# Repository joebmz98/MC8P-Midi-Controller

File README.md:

# MC8P Standalone MIDI Controller

---

# **8-Pot Standalone MIDI Controller (Teensy 4.0)**

A customizable, open-source MIDI controller with **8 potentiometers**, each supporting **Up to 10 assignable MIDI CCs per Potentiometer**, built around the **Teensy 4.0** for high-performance MIDI control.

---
## Introducing the MC8P Video

---

## **Features**
- **8x B100K Pots** with smooth analog control
- **Teensy 4.0** for fast, reliable MIDI
- **SSD1306 I2C OLED (128x64)** for the UI
- **Per-Pot CC Assignment** – Each pot can send **10 different MIDI CCs**
- **3.5mm MIDI TRS Out** (PJ307 socket for Type A MIDI)
- **4x Kailh Switches** for UI navigation/configuration
- **Standalone Operation** – No computer needed after setup
- **Open-Source Firmware** (Arduino IDE-compatible)

---

## **Bill of Materials (BOM)**

| Component                  | Qty | Notes                          | Links |
|----------------------------|-----|--------------------------------|-------|
| Teensy 4.0                 | 1   | Main microcontroller           | [The Pi Hut (UK)](https://thepihut.com/products/pjrc-teensy-4-0-usb-development-board) |
| SSD1306 OLED (128×64)      | 1   | I²C interface                  | [AliExpress](https://www.aliexpress.com/item/1005006997755041.html) |
| B100K Vertical Potentiometer | 8  | Linear taper                   | [Example](https://shorturl.at/ZGaz2) |
| 3.5mm Stereo Socket (PJ307) | 1  | MIDI TRS Type A                | [Example](https://shorturl.at/lp2T3) |
| Kailh Switches             | 4   | For menu navigation            | —     |
| Kailh Switch Caps          | 4   | For Kailh switches             | [AliExpress](https://www.aliexpress.com/item/1005006477890497.html) |
| Potentiometer Knobs        | 8   | For B100K potentiometers       | [AliExpress](https://www.aliexpress.com/item/1005006064249289.html) |
| DC-005 Barrel Jack Socket  | 1   | 5V DC power input              | [AliExpress](https://www.aliexpress.com/item/32839712664.html) |
| 10nF Ceramic Capacitors    | 8   | Potentiometer filtering        | —     |
| 10k Resistors              | 4   | Pull-down for buttons          | —     |
| 220Ω Resistors             | 2   | For MIDI Circuitry             | —     |
| 100nF Ceramic Capacitor    | 1   | Power rail stabilisation       | —     |
| 10uF Ceramic Capacitor     | 1   | Power rail stabilisation       | —     |
| 10uF Electrolytic Capacitor| 1   | 5V input stability             | —     |
| 100uF Electrolytic Capacitor | 1 | Power rail stabilisation       | —     |

---

## **Available Purchase Options**
**PCB Only** – For custom builds → [**Purchase from my Tindie store**](https://www.tindie.com/products/axsinstruments/diy-mc8p-standalone-midi-controller-pcbs-only/)

---

## **Installation & Setup**
### **1. Flashing the Firmware**
- Install **Arduino IDE + Teensyduino** and other dependencies referenced in the Building from Source section
- Clone this repo and open the `.ino` file in the Arduino IDE
- Select **Teensy 4.0** in Arduino IDE
- Upload the firmware

### **2. Hardware Assembly**
- Refer to the *Build Guide*

### **3. First Boot**
- Power via **USB** on the Teensy or via DC-005 input jack 
- Use the **OLED menu** to assign CCs

---

## **Configuration**

### Button Functions

| Button | Primary Function |
|--------|-----------------|
| ASSIGN | Navigate backward, cancel actions, return to previous screens |
| ENTER | Confirm selections, activate temporary override mode |
| PREV | Move up or decrease values |
| NEXT | Move down or increase values |

### Screen Hierarchy

The interface is organized into several screens accessible from the main display:

**MAIN SCREEN** → **MENU** → **SETTINGS** → various configuration screens

### Main Screen

This is your default operating view. The screen displays eight circular indicators, one for each potentiometer, showing current MIDI values (0-127). Each circle fills proportionally to the value being sent.

From the main screen:
- Press **ASSIGN** to open the menu
- Press and hold **ENTER** to activate temporary override mode (the display inverts as visual feedback)

### Temporary Override Mode

When you press and hold ENTER on the main screen, the controller enters temporary override mode. In this mode, all potentiometer adjustments are temporary. When you release ENTER, the controller returns to the stored values and activates catch up mode, where potentiometers must pass through their stored positions before taking control again.

### Menu Screen

Press ASSIGN from the main screen to reach the menu. Use PREV and NEXT to scroll through options:

- **CC assign** – Configure MIDI messages for each potentiometer
- **Settings** – Access device configuration

Press ENTER to select an option, or press ASSIGN to return to the main screen.

### Assign Screen (CC Assign)

This screen lets you configure up to 10 MIDI messages per potentiometer.

**Navigation flow:**
1. Select which potentiometer to edit (flashing number)
2. Select which message slot to edit, or choose Add/Remove
3. Edit individual parameters

**Parameters you can edit for each message:**
- **Channel** – MIDI channel (1-16) or OMNI
- **CC** – Control Change number (0-127)
- **Min Value** – Minimum output value (0-127)
- **Max Value** – Maximum output value (0-127)
- **Direction** – Normal (0-127) or Inverted (127-0)

**Editing values:** When editing a parameter, use potentiometer 8 to smoothly adjust the value across its full range. The selected parameter flashes to indicate edit mode.

**Navigation within Assign Screen:**
- **PREV/NEXT** – Navigate between pots, messages, or Add/Remove buttons
- **ENTER** – Enter edit mode for a parameter, or cycle to the next parameter
- **ASSIGN** – Return to pot selection, or save and exit (confirmation popup appears)

**Add/Remove messages:**
- Navigate to "+ Add" to create a new message (up to 10 per pot)
- Navigate to "- Remove" to delete the selected message (minimum 1 message per pot)

### Settings Screen

From the menu, select Settings to access:

**Assign Settings** – Choose which potentiometer (1-8) to use for editing values in the Assign screen. Use PREV/NEXT to change the selection.

**Display Settings** – Toggle the display inversion between normal and inverted. Press ENTER to enter edit mode, then use PREV or NEXT to toggle between Yes and No. Press ENTER again to save, or ASSIGN to cancel.

**About** – View firmware version and device information.

**Factory Reset** – Restore all settings to default values. A confirmation screen prevents accidental resets.

### Confirmation Popups

When saving changes or performing a factory reset, a popup screen appears asking for confirmation. Use PREV/NEXT to toggle between Y (Yes) and N (No), then press ENTER to confirm or ASSIGN to cancel.

---

## **MIDI Implementation**
- USB MIDI **OR** TRS MIDI Out (3.5mm Type A)
- Up to **10 CC Messages** per potentiometer - further expansion maybe soon!

---

## **Building from Source**
- Requires **Arduino IDE + Teensyduino**
- Libraries:
  - `Adafruit_SSD1306` (OLED)
  - `Adafruit_GFX` (Adafruit UI Design)
  - `MIDI` (MIDI)
  - `ResponsiveAnalogRead` (Potentiometer Smoothing)
  - `Picopixel` (Picopixel Font)

**Owner's Manual:** https://docs.google.com/document/d/1LK1hT5nvRXzgEnc-npS-HN6GpmSG35B1l2-KNDyIfV0/edit?usp=sharing

---

## **License**
**MIT License** – Open-source for personal & commercial use

---

## **Support & Contributions**
- **Issues:** Open a GitHub ticket
- **Custom Requests:** Start a thread in the discussions page or send me an E-mail! axs.instruments@gmail.com
- **Want to improve it?** PRs welcome!
- **Special Thanks:** This project is supported by **PCBWay** who have kindly provided the PCB stock available at the moment

---

## **Acknowledgments**

PCBway very kindly offered to sponsor this project and have sent me some more stock for the shop. Thank you to PCBway for supporting this passion project of mine. Emily from the marketing department reached out to me when I first launched the product and store and very kindly offered to sponsor the project. Both working with them and using their services was really easy. All I needed to do was export my PCB gerber files, drag and drop them on the 'PCB Instant Quote' page and send it off for approval. I received my order a week later and was very happy with the quality of the PCBs. Thank you again PCBway for your support.

You can find their website here: https://www.pcbway.com/

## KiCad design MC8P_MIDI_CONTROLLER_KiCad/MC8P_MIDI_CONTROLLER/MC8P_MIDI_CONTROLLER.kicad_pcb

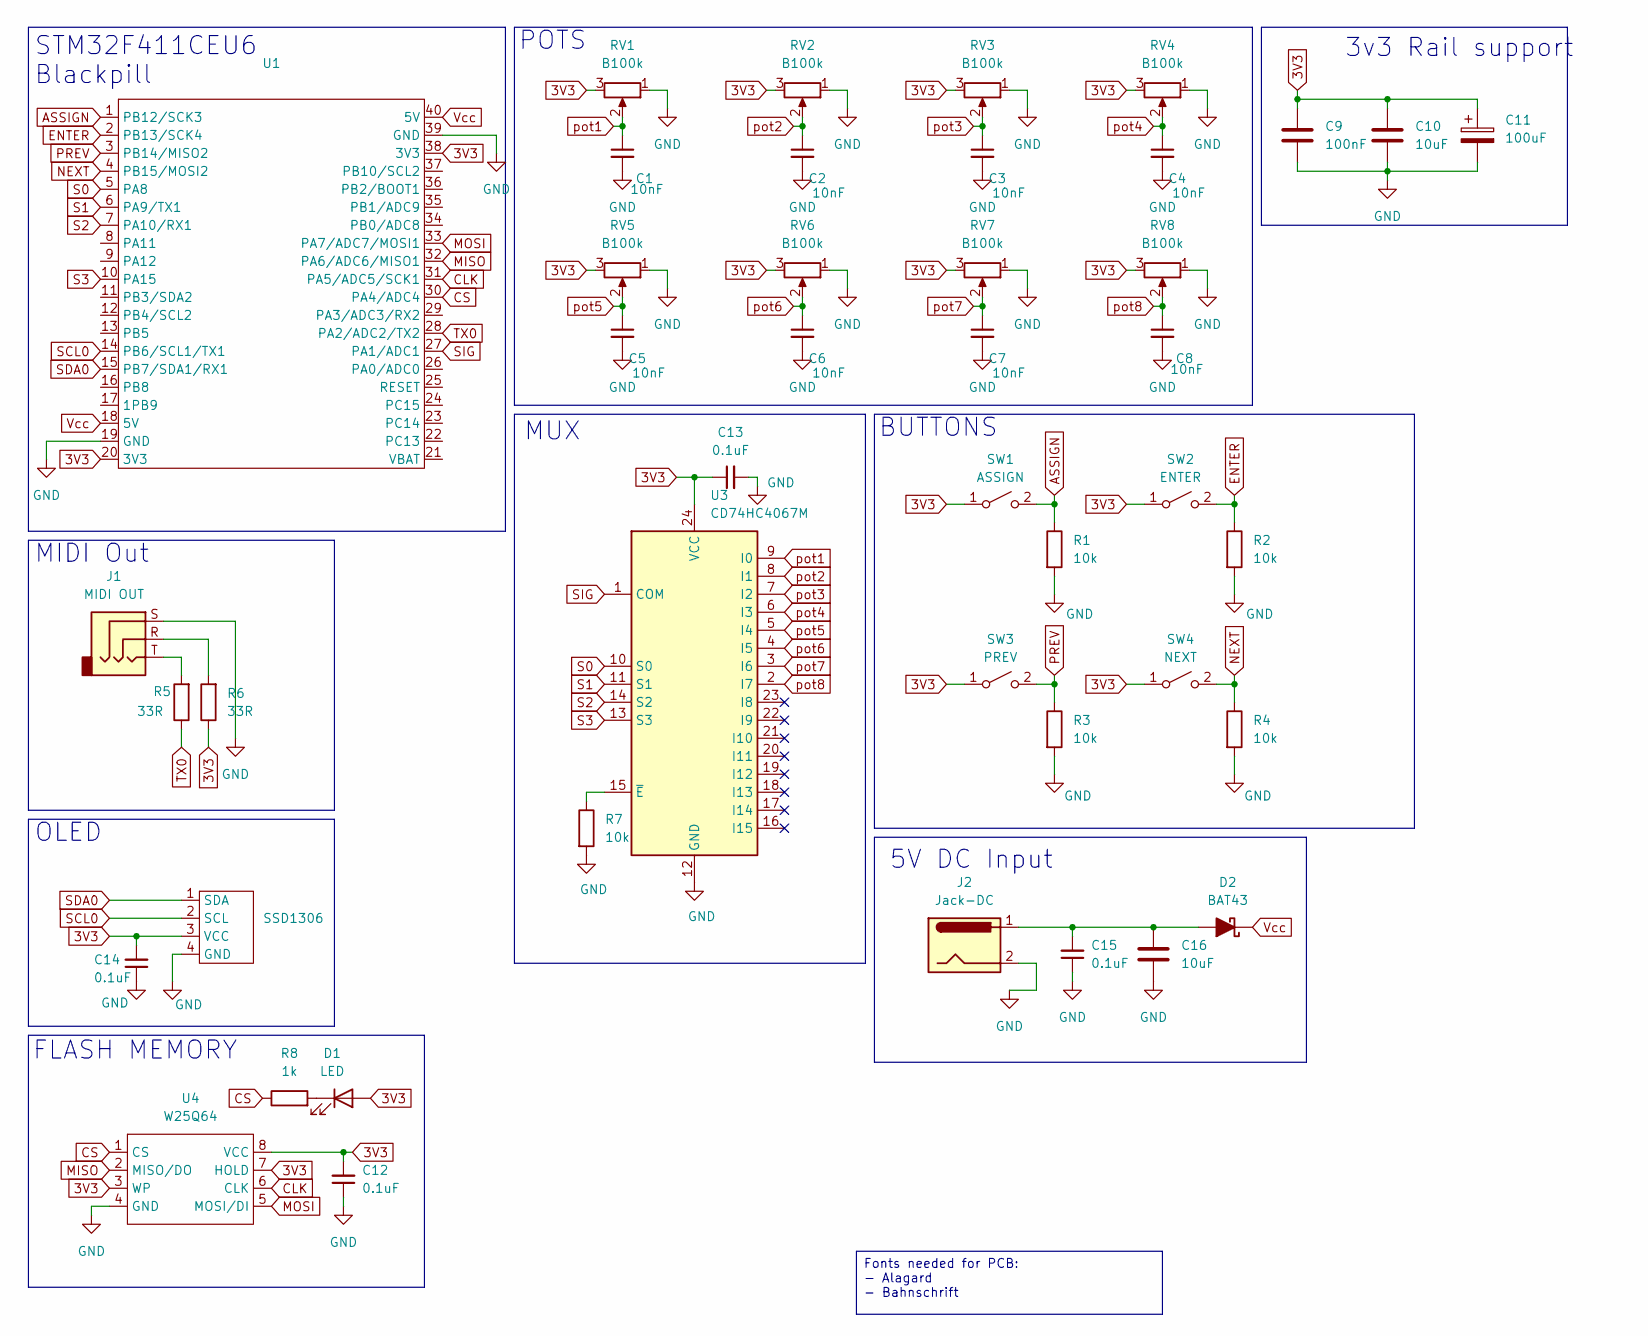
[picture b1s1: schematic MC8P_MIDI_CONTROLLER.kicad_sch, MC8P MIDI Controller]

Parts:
C1, C2, C3, C4, C5, C6, C7, C8: C_Generic; C_1206_3216Metric_Pad1.33x1.80mm_HandSolder
C9: 100nF; C_1206_3216Metric_Pad1.33x1.80mm_HandSolder
C10, C16: 10uF; C_1206_3216Metric_Pad1.33x1.80mm_HandSolder
C11: 100uF; CP_Radial_D4.0mm_P1.50mm
C12, C13, C14, C15: 100nF_0603_16V; C_1206_3216Metric; Part Number 0603YC104KAT2A; JLCPCB ID C14663
D1: LED; LED_1206_3216Metric_Pad1.42x1.75mm_HandSolder
D2: BAT43; D_SOD-123
J1: MIDI OUT; Jack_3.5mm_CUI_SJ1-3525N_Horizontal_edit
J2: Jack-DC; BarrelJack_GCT_DCJ200-10-A_Horizontal
R1, R2, R3, R4: 10k; R_0603; Part Number RT0402FRE0710KL
R5, R6: 220R; R_0603; Part Number RT0402FRE0710KL
R7, R8: 10k_0402; R_0603; Part Number RT0402FRE0710KL
RV1, RV2, RV3, RV4, RV5, RV6, RV7, RV8: B100k; Potentiometer_RV09_BigPads
SSD1306: SSD1306_OLED_Module
SW1: ASSIGN; SW_Cherry_MX_1.00u_PCB
SW2: ENTER; SW_Cherry_MX_1.00u_PCB
SW3: PREV; SW_Cherry_MX_1.00u_PCB
SW4: NEXT; SW_Cherry_MX_1.00u_PCB
U1: Z_module_black_pill_STM32F411
U3: CD74HC4067M; SOIC-24W_7.5x15.4mm_P1.27mm
U4: W25Q64; SOIC-8_3.9x4.9mm_P1.27mm

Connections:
3V3: C9.1, C10.1, C11.1, C12.2, C13.1, C14.2, D1.2 (A), R6.1, RV1.3, RV2.3, RV3.3, RV4.3, RV5.3, RV6.3, RV7.3, RV8.3, SSD1306.3 (VCC), SW1.1 (A), SW2.1 (A), SW3.1 (A), SW4.1 (A), U1.20 (3V3), U1.38 (3V3), U3.24 (VCC), U4.3 (WP), U4.7 (HOLD), U4.8 (VCC)
ASSIGN: R1.1, SW1.2 (B), U1.1 (PB12/SCK3)
CLK: U1.31 (PA5/ADC5/SCK1), U4.6 (CLK)
CS: R8.1, U1.30 (PA4/ADC4), U4.1 (CS)
ENTER: R2.1, SW2.2 (B), U1.2 (PB13/SCK4)
GND: C1.2, C2.2, C3.2, C4.2, C5.2, C6.2, C7.2, C8.2, C9.2, C10.2, C11.2, C12.1, C13.2, C14.1, C15.1, C16.2, J1.S, J2.2, R1.2, R2.2, R3.2, R4.2, R7.2, RV1.1, RV2.1, RV3.1, RV4.1, RV5.1, RV6.1, RV7.1, RV8.1, SSD1306.4 (GND), U1.19 (GND), U1.39 (GND), U3.12 (GND), U4.4 (GND)
MISO: U1.32 (PA6/ADC6/MISO1), U4.2 (MISO/DO)
MOSI: U1.33 (PA7/ADC7/MOSI1), U4.5 (MOSI/DI)
NEXT: R4.1, SW4.2 (B), U1.4 (PB15/MOSI2)
unnamed: D1.1 (K), R8.2
unnamed: C15.2, C16.1, D2.2 (A), J2.1
unnamed: J1.R, R6.2
unnamed: J1.T, R5.2
unnamed: R7.1, U3.15 (~E)
PREV: R3.1, SW3.2 (B), U1.3 (PB14/MISO2)
S0: U1.5 (PA8), U3.10 (S0)
S1: U1.6 (PA9/TX1), U3.11 (S1)
S2: U1.7 (PA10/RX1), U3.14 (S2)
S3: U1.10 (PA15), U3.13 (S3)
SCL0: SSD1306.2 (SCL), U1.14 (PB6/SCL1/TX1)
SDA0: SSD1306.1 (SDA), U1.15 (PB7/SDA1/RX1)
SIG: U1.27 (PA1/ADC1), U3.1 (COM)
TX0: R5.1, U1.28 (PA2/ADC2/TX2)
Vcc: D2.1 (K), U1.18 (5V), U1.40 (5V)
pot1: C1.1, RV1.2, U3.9 (I0)
pot2: C2.1, RV2.2, U3.8 (I1)
pot3: C3.1, RV3.2, U3.7 (I2)
pot4: C4.1, RV4.2, U3.6 (I3)
pot5: C5.1, RV5.2, U3.5 (I4)
pot6: C6.1, RV6.2, U3.4 (I5)
pot7: C7.1, RV7.2, U3.3 (I6)
pot8: C8.1, RV8.2, U3.2 (I7)

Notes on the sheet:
STM32F411CEU6 Blackpill
5V DC Input
3v3 Rail support
POTS
MUX
FLASH MEMORY
BUTTONS
MIDI Out
OLED
Fonts needed for PCB: - Alagard - Bahnschrift

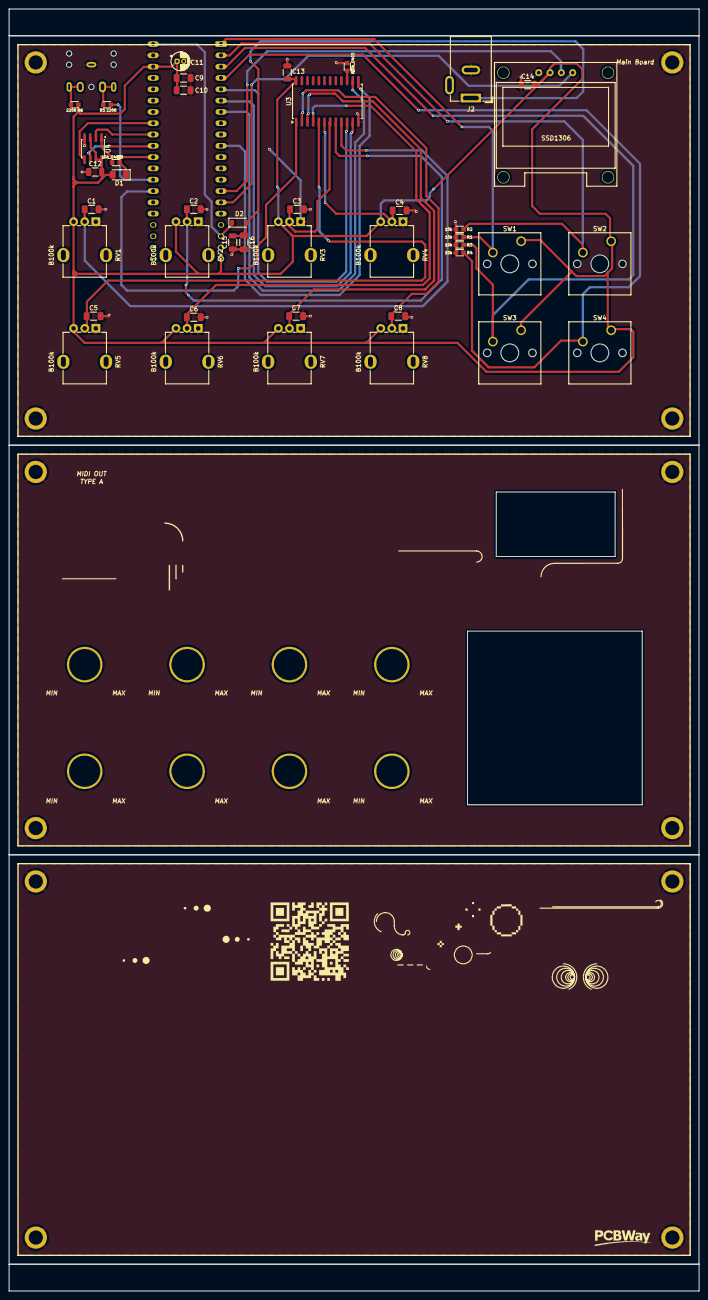
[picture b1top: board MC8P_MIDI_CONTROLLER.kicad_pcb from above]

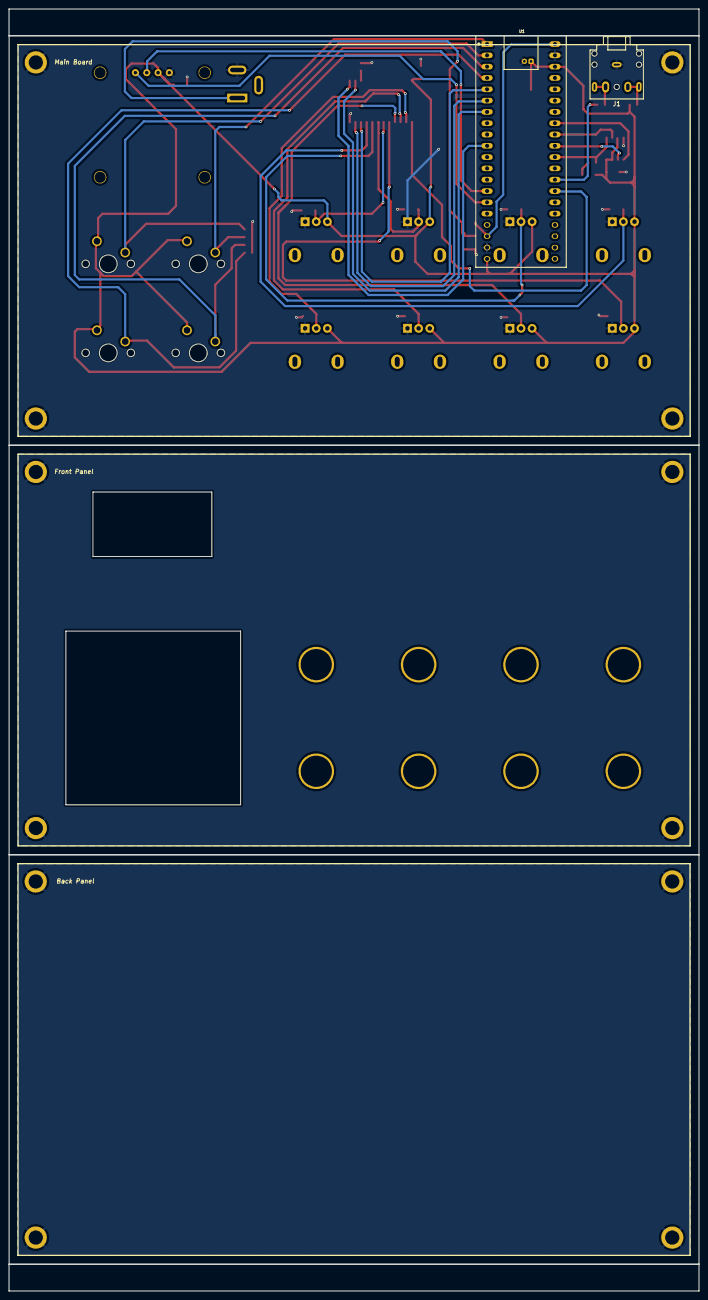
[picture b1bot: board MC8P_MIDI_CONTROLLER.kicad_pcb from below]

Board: 2 copper layers, 155.0 x 288.0 mm, 44 parts (3 on the bottom side), 32 nets.

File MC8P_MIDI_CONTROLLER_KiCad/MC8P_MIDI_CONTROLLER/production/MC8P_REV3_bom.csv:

Designator,Footprint,Quantity,Value,LCSC Part #
"_9, _8, _7, _6, _5, _4, _3, _2, ",,9,,
"C1, C2, C3, C4, C5, C6, C7, C8",1206,8,C_Generic,
"C10, C16",1206,2,10uF,
C11,CP_Radial_D4.0mm_P1.50mm,1,100uF,
"C12, C13, C14, C15",1206,4,100nF_0603_16V,
C9,1206,1,100nF,
D1,1206,1,LED,
D2,1206,1,BAT43,
J1,Jack_3.5mm_CUI_SJ1-3525N_Horizontal_edit,1,MIDI OUT,
J2,BarrelJack_GCT_DCJ200-10-A_Horizontal,1,Jack-DC,
"R1, R2, R3, R4",R_0603,4,10k,
"R5, R6",R_0603,2,220R,
"R7, R8",R_0603,2,10k_0402,
"RV1, RV2, RV3, RV4, RV5, RV6, RV7, RV8",Potentiometer_RV09_BigPads,8,B100k,
SSD1306,SSD1306_OLED_Module,1,~,
SW1,SW_Cherry_MX_1.00u_PCB,1,ASSIGN,
SW2,SW_Cherry_MX_1.00u_PCB,1,ENTER,
SW3,SW_Cherry_MX_1.00u_PCB,1,PREV,
SW4,SW_Cherry_MX_1.00u_PCB,1,NEXT,
U1,Z_module_black_pill_STM32F411,1,~,
U3,SOIC-24W_7.5x15.4mm_P1.27mm,1,CD74HC4067M,
U4,SOIC-8_3.9x4.9mm_P1.27mm,1,W25Q64,

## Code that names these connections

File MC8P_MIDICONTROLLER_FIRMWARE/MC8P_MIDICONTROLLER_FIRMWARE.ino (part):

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// -- BUTTON CONFIG
const int NUM_BUTTONS = 4;
const int BUTTON_PINS[NUM_BUTTONS] = { 5, 6, 7, 8 };
const char* BUTTON_NAMES[NUM_BUTTONS] = { "ASSIGN", "ENTER", "PREV", "NEXT" };
int buttonState[NUM_BUTTONS] = { 0 };
int lastButtonState[NUM_BUTTONS] = { 0 };
unsigned long lastDebounceTime[NUM_BUTTONS] = { 0 };
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

// MENU NAVIGATION
int selectedMenuItem = 0;  // 0: Assign, 1: States, 2: Settings

// BUTTON STATE MANAGEMENT
// ASSIGN
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bool tempOverrideActive = false;                // Flag for temporary override mode
int originalMidiValues[N_POTS] = { 0 };         // Store original values when ENTER is pressed - INIT TO 0
int tempMidiValues[N_POTS] = { 0 };             // Store temporary values during override - INIT TO 0
unsigned long enterPressTime = 0;               // Time when ENTER was pressed
const unsigned long tempOverrideHoldTime = 20;  // Debounce time to activate override
int postOverridePotPositions[N_POTS] = { 0 };   // Store pot positions when temp override ends - INIT TO 0
bool catchUpActive[N_POTS] = { false };         // Flag to track if catch-up is active for each pot - INIT TO FALSE
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                  saveGlobalSettingsToEEPROM();
                  // Go back to SETTINGS_SCREEN
                  currentScreen = SETTINGS_SCREEN;
                  selectedMenuItem = 0;  // Keep Assign Settings selected
                  Serial.println("ASSIGN pressed - saving and returning to SETTINGS_SCREEN");
                }
              } else if (currentScreen == SETTINGS_SCREEN) {
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
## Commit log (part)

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2025-08-14 v.1.0
    - Added KiCad Files
    - Added the Firmware
2025-08-14 V1.0.1
    - Added Owner's Manual
    - Removed clutter files
2025-08-14 V1.0.2
    - KiCad Modifications
2025-08-14 Created Solder Mask QR
2025-08-14 v1.0.3
    - Back panel finalised
    - Exported gerbers
    - Panelised for DIY kits
2025-08-14 Gerber Edits
2025-08-15 Create LICENSE
2025-08-15 v1.0.4
    - Design update with new logo
2025-08-18 v1.0.6
    -Adjustments to Front Panel and button positions
    - Beginning Blender Models
2025-08-18 v1.0.7
    -Model Updates
2025-08-18 v1.0.8
    - New model
2025-08-18 v1.0.8
    - First renders
2025-08-18 v1.0.9
    - Panel alterations
    - Sketchup alterations
2025-08-19 v.1.0.10
    - Adding Models for pots
2025-08-20 v1.0.13
    - Blender models update
2025-08-22 v1.0.7
2025-08-22 v1.10
    - UI Vectors
2025-08-29 v1.1.0
    - PCB Fixes
    - firmware descriptor adjustments
2025-08-30 Firmware v1.1
    -Button Debounce time adjustments
    -Include MIT Licenser reference
2025-08-30 Schematic update v1.2.0
    - Added Bulk capacitors between the 5V and 3V3 power rails to ground for power stabilisation
    - Added Decoupling capacitor between the power rails and ground for high frequency noise filtering
2025-08-31 Build Completion Media
    - Added Photos of physical product
    - Added Video showcasing the controller
2025-08-31 V1.1.1
    Visual firmware changes
2025-09-01 Power stability
    - Added capacitors to add power stability
    - Adjusted Front panel + gerbers
    - Adjusted Main Board + gerbers
    - Re-frabricated panel gerbers
2025-09-11 Updated Manual and Build Guide
2025-10-30 PCB Update
    - Fixes power resets/brownouts
    - disconnected POTS, BUTTONS and MIDI OUT from Vin
    - connected POTS & BUTTONS to 3V3
    - connected MIDI OUT to VUSB
2025-10-30 Schematic & PCB labelling update
    Updated Capacitor labelling (C9-11)
2026-01-24 Firmware 1.2.0
    - Added temporary modify function. Hold the ENTER button in the performance mode to temporarily adjust midi parameters. Upon release, the values will return to their original value. Potentiometers wi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
2026-01-28 v1.3
    - Fixed USB Descriptor
    - Made a variable for changing firmware version
2026-01-28 v1.3
2026-02-03 IMAGES
    Product Images
2026-02-03 Updated Owners Guide
2026-02-03 Folder structure changes
2026-02-12 Menus
    - Added new Menu System
    - Added Display invert settings
    - Display settings save to EEPROM
2026-02-13 beta 2.0
2026-03-28 PCB Updates
    - Added dedicated 5V Centre Positive power input
    - Added PCBWay logo for sponsor
    - Updated UI Components with new Alagard font
2026-03-29 v2.0
2026-03-30 fw 2.0
2026-04-01 v2.0
    USB MIDI
2026-04-01 v2.0
    Screen bug fixes
2026-04-01 v2.0
    fixed max value button order
2026-04-01 v2.0
    removed old button functions and unused variables from readbuttons()
2026-04-01 v2.0
    - factory reset bug with missing midi messages
2026-04-01 v2.0
    Fixed catchup for TEMP mode
2026-04-01 v2.0
    -Fixed USB Descriptor
2026-04-01 v2.0
    Fixed visual bug in temp mode with pot values
2026-04-03 Documentation update
2026-04-12 Added scenes control
2026-04-12 Scenes menu
2026-04-13 Updated scenes menu
2026-04-13 Custom Scene sequences
2026-04-13 Scene modes
2026-04-13 Scenes
    - Added Scene functionality
    - Using the NEXT/PREV buttons you can navigate between Scenes on the OP-XY. The MIDI CC of the scene change can be changed in the menu
2026-04-13 MIDI CC Curves
2026-05-06 PCB Rev3
    - STM32F411CEU6 Black Pill with
    W25Q64 flash
    - Added DC Jack for powering externally
    - restructured KiCad Folder
    - Added production folder with BOM
2026-05-14 PCB revisions

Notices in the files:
MC8P_MIDICONTROLLER_FIRMWARE/MC8P_MIDICONTROLLER_FIRMWARE.ino:
This project is released under the MIT License.
Copyright (c) 2024 .axs instruments
